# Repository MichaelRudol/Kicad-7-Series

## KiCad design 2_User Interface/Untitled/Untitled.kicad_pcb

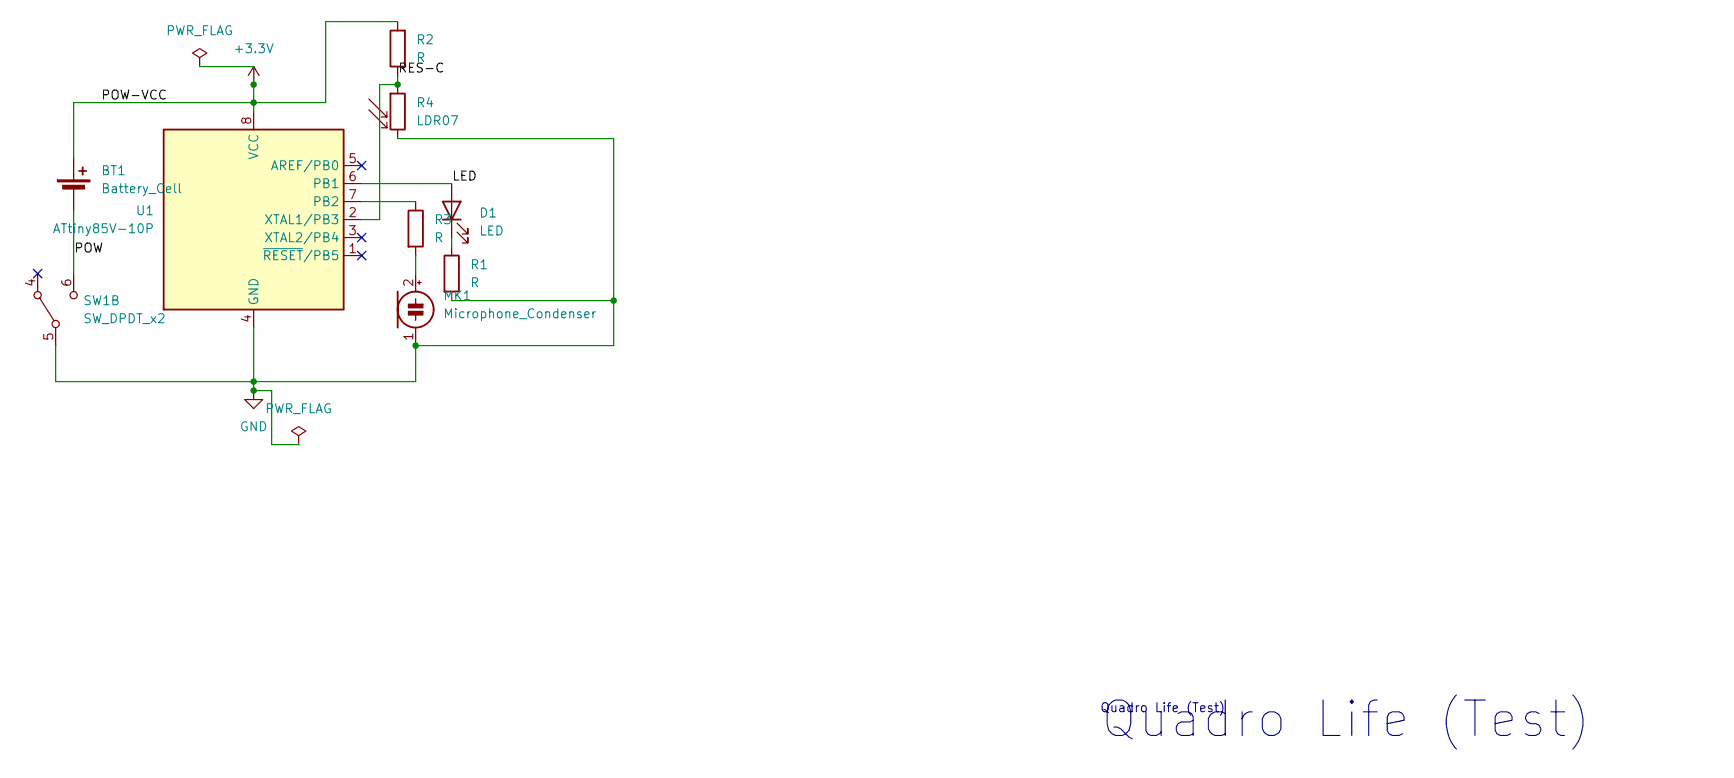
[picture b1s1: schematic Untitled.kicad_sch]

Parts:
BT1: Battery_Cell; BatteryHolder_ComfortableElectronic_CH273-2450_1x2450
D1: LED; LED_D4.0mm
MK1: Microphone_Condenser; PinHeader_1x02_P2.54mm_Vertical
R1, R2, R3: R; R_Axial_DIN0309_L9.0mm_D3.2mm_P25.40mm_Horizontal
R4: LDR07; R_Axial_DIN0309_L9.0mm_D3.2mm_P25.40mm_Horizontal
SW1: SW_DPDT_x2; SW_CuK_JS202011AQN_DPDT_Angled
U1: ATtiny85V-10P; DIP-8_W7.62mm

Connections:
+3.3V: BT1.1 (+), R2.2, U1.8 (VCC)
/LED: D1.2 (A), U1.6 (PB1)
/POW: BT1.2 (-), SW1.6 (C)
/RES-C: R2.1, R4.1, U1.2 (XTAL1/PB3)
GND: MK1.1 (-), R1.2, R4.2, SW1.5 (B), U1.4 (GND)
unnamed: D1.1 (K), R1.1
unnamed: MK1.2 (+), R3.2
unnamed: R3.1, U1.7 (PB2)

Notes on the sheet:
Quadro Life (Test)

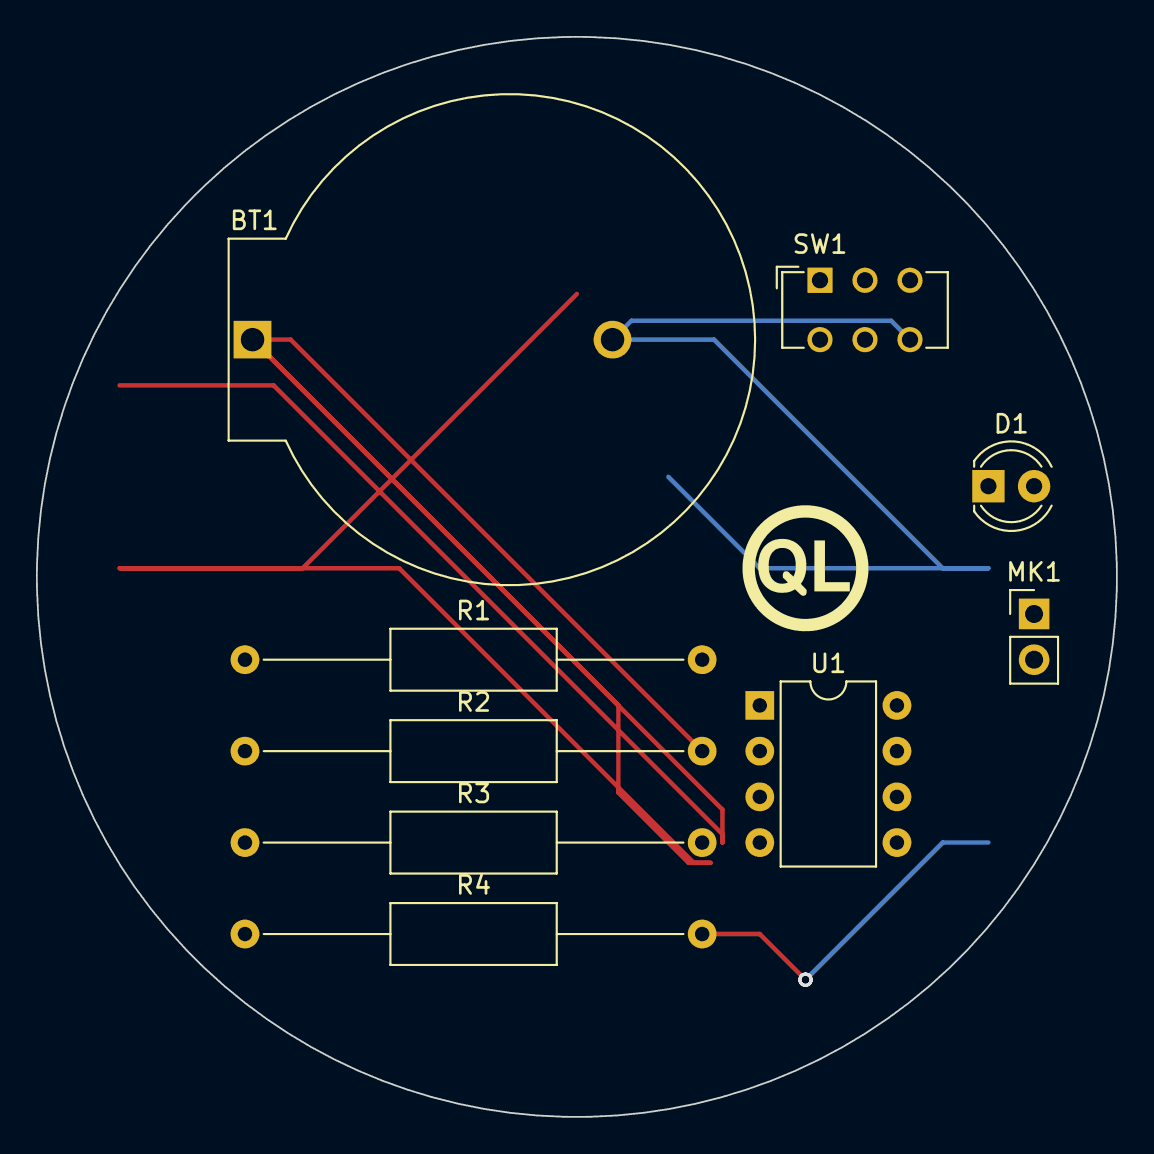
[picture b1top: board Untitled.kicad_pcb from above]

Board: 2 copper layers, 60.0 x 60.0 mm, 9 parts (0 on the bottom side), 8 nets.

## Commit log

2023-09-15 CommitToMainTest
    Test 01
